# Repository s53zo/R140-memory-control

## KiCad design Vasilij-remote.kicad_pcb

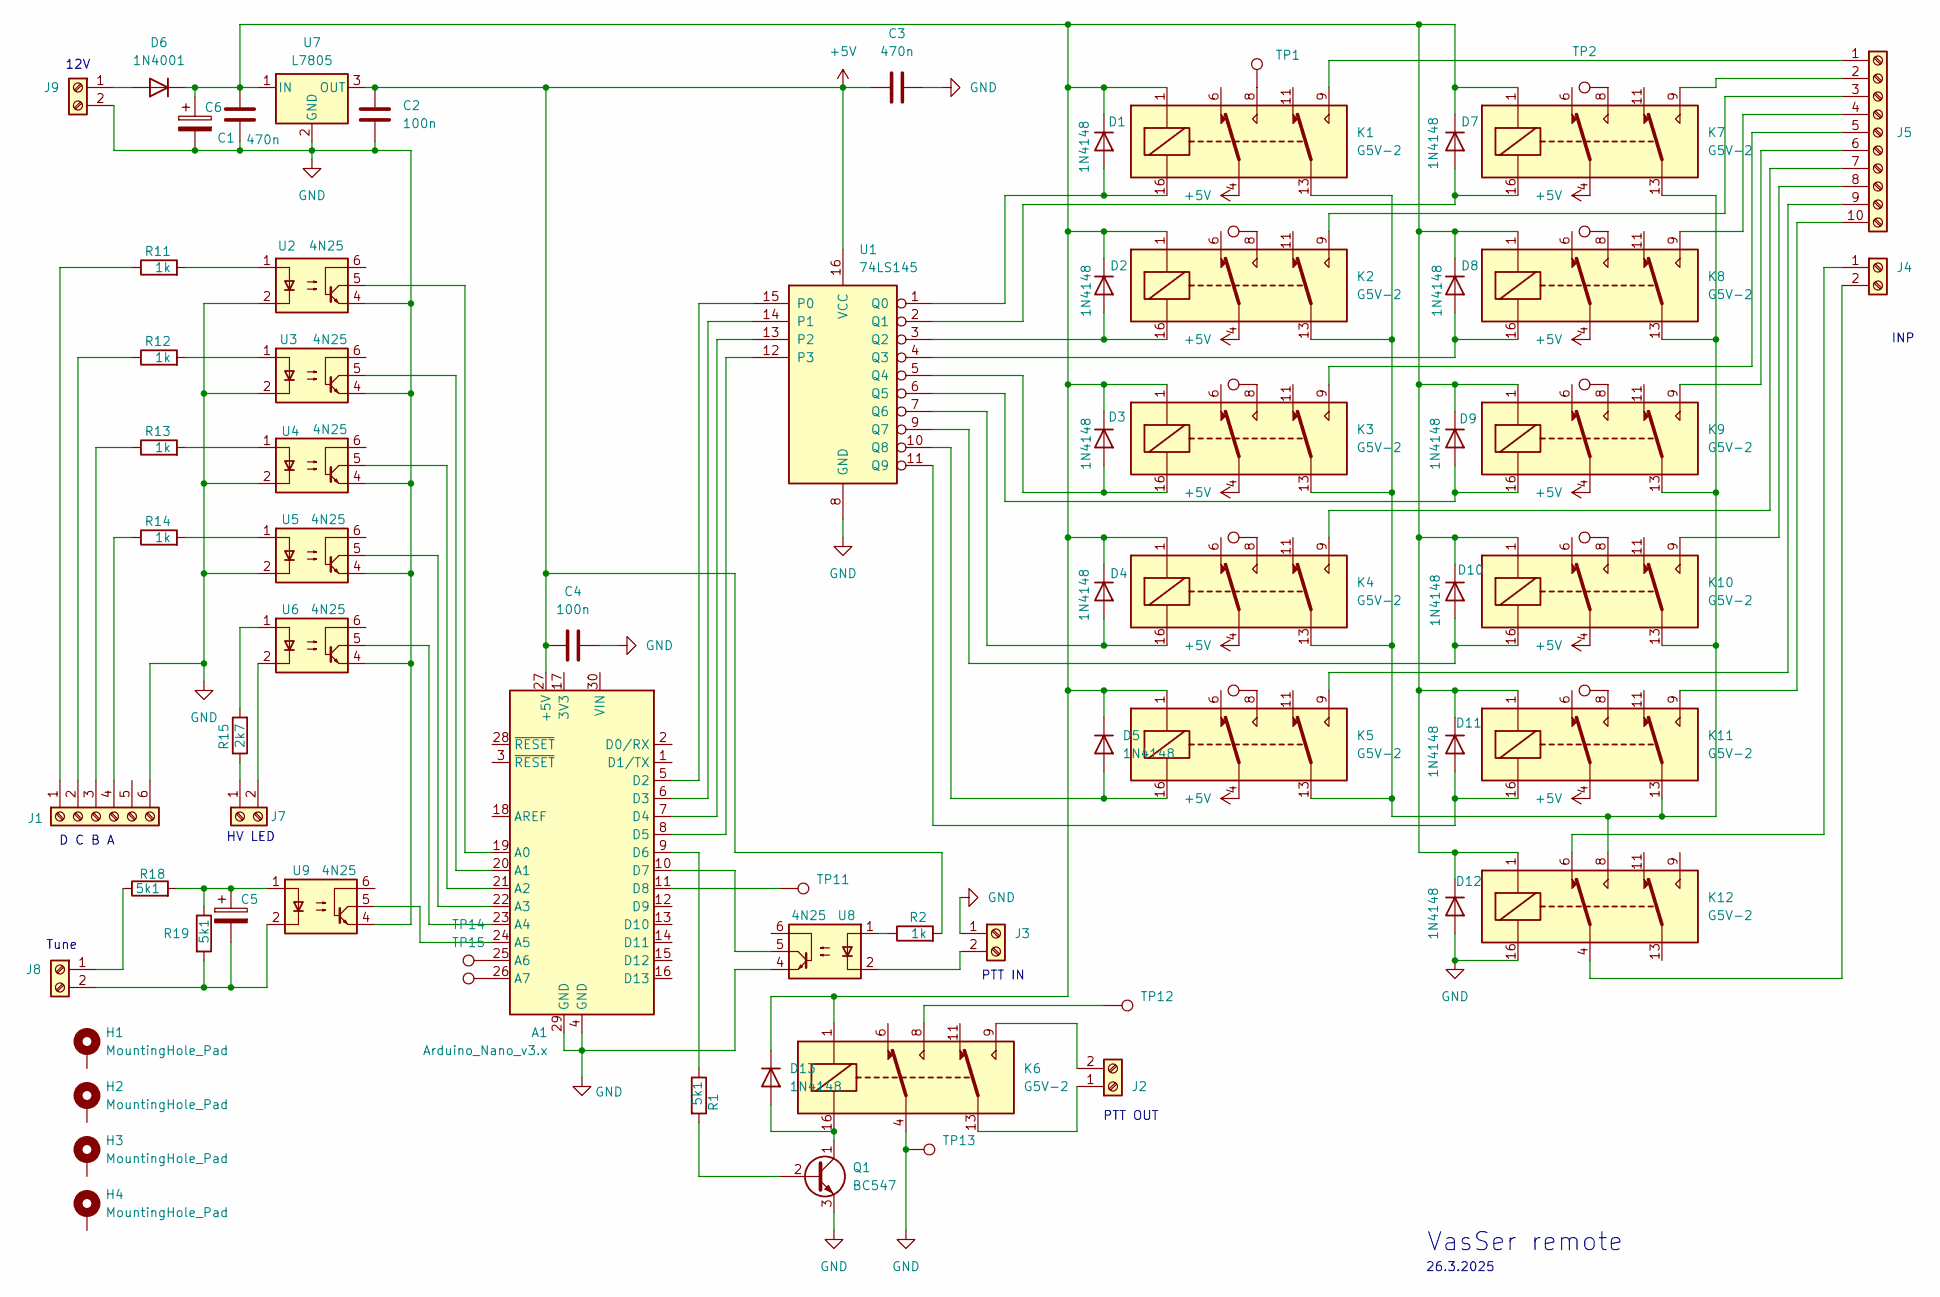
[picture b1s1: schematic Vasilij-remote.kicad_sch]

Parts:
A1: Arduino_Nano_v3.x; Arduino_Nano
C1, C3: 470n; C_Axial_L3.8mm_D2.6mm_P7.50mm_Horizontal
C2: 100n; C_Axial_L3.8mm_D2.6mm_P7.50mm_Horizontal
C4: 100n; C_Disc_D4.3mm_W1.9mm_P5.00mm
C5, C6: 100uF; CP_Radial_D5.0mm_P2.00mm
D1, D2, D3, D4, D5, D7, D8, D9, D10, D11, D12, D13: 1N4148; D_DO-34_SOD68_P7.62mm_Horizontal
D6: 1N4001; D_DO-41_SOD81_P10.16mm_Horizontal
H1, H2, H3, H4: MountingHole_Pad; MountingHole_3.2mm_M3_DIN965_Pad
J1: Screw_Terminal_01x06; TerminalBlock_Xinya_XY308-2.54-6P_1x06_P2.54mm_Horizontal
J2, J3, J4, J7, J8, J9: Screw_Terminal_01x02; TerminalBlock_Xinya_XY308-2.54-2P_1x02_P2.54mm_Horizontal
J5: Screw_Terminal_01x10; TerminalBlock_Xinya_XY308-2.54-10P_1x10_P2.54mm_Horizontal
K1, K2, K3, K4, K5, K6, K7, K8, K9, K10, K11, K12: G5V-2; Relay_DPDT_Omron_G5V-2
Q1: BC547; TO-92_Inline
R1, R18, R19: 5k1; R_Axial_DIN0204_L3.6mm_D1.6mm_P5.08mm_Horizontal
R2, R11, R12, R13, R14: 1k; R_Axial_DIN0204_L3.6mm_D1.6mm_P5.08mm_Horizontal
R15: 2k7; R_Axial_DIN0204_L3.6mm_D1.6mm_P5.08mm_Horizontal
TP1, TP2, TP3, TP4, TP5, TP6, TP7, TP8, TP9, TP10, TP11, TP12, TP13, TP14, TP15: TestPoint; Pin_D0.7mm_L6.5mm_W1.8mm_FlatFork
U1: 74LS145; DIP-16_W7.62mm
U2, U3, U4, U5, U6, U8, U9: 4N25; DIP-6_W7.62mm
U7: L7805; TO-220F-3_Vertical

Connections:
+5V: A1.27 (+5V), C2.1, C3.1, C4.1, K1.4, K2.4, K3.4, K4.4, K5.4, K7.4, K8.4, K9.4, K10.4, K11.4, R2.2, U1.16 (VCC), U7.3 (OUT)
GND: A1.4 (GND), A1.29 (GND), C1.2, C2.2, C3.2, C4.2, C6.2, D12.2 (A), J1.6, J3.1, J9.2, K6.4, K12.16, Q1.3 (E), TP13.1, U1.8 (GND), U2.2, U2.4, U3.2, U3.4, U4.2, U4.4, U5.2, U5.4, U6.4, U7.2 (GND), U8.4, U9.4
unnamed: A1.19 (A0), U2.5
unnamed: A1.20 (A1), U3.5
unnamed: A1.21 (A2), U4.5
unnamed: A1.22 (A3), U5.5
unnamed: A1.23 (A4), U6.5
unnamed: A1.24 (A5), U9.5
unnamed: A1.25 (A6), TP14.1
unnamed: A1.26 (A7), TP15.1
unnamed: A1.5 (D2), U1.15 (P0)
unnamed: A1.6 (D3), U1.14 (P1)
unnamed: A1.7 (D4), U1.13 (P2)
unnamed: A1.8 (D5), U1.12 (P3)
unnamed: A1.9 (D6), R1.1
unnamed: A1.10 (D7), U8.5
unnamed: A1.11 (D8), TP11.1
unnamed: C5.1, R18.2, R19.1, U9.1
unnamed: D1.2 (A), K1.16, U1.1 (Q0)
unnamed: C1.1, C6.1, D1.1 (K), D2.1 (K), D3.1 (K), D4.1 (K), D5.1 (K), D6.1 (K), D7.1 (K), D8.1 (K), D9.1 (K), D10.1 (K), D11.1 (K), D12.1 (K), D13.1 (K), K1.1, K2.1, K3.1, K4.1, K5.1, K6.1, K7.1, K8.1, K9.1, K10.1, K11.1, K12.1, U7.1 (IN)
unnamed: D2.2 (A), K2.16, U1.3 (Q2)
unnamed: D3.2 (A), K3.16, U1.5 (Q4)
unnamed: D4.2 (A), K4.16, U1.7 (Q6)
unnamed: D5.2 (A), K5.16, U1.10 (Q8)
unnamed: D6.2 (A), J9.1
unnamed: D7.2 (A), K7.16, U1.2 (Q1)
unnamed: D8.2 (A), K8.16, U1.4 (Q3)
unnamed: D9.2 (A), K9.16, U1.6 (Q5)
unnamed: D10.2 (A), K10.16, U1.9 (Q7)
unnamed: D11.2 (A), K11.16, U1.11 (Q9)
unnamed: D13.2 (A), K6.16, Q1.1 (C)
unnamed: J1.1, R11.1
unnamed: J1.2, R12.1
unnamed: J1.3, R13.1
unnamed: J1.4, R14.1
unnamed: J2.1, K6.13
unnamed: J2.2, K6.9
unnamed: J3.2, U8.2
unnamed: J4.1, K12.6
unnamed: J4.2, K12.4
unnamed: J5.1, K1.9
unnamed: J5.2, K7.9
unnamed: J5.3, K2.9
unnamed: J5.4, K8.9
unnamed: J5.5, K3.9
unnamed: J5.6, K9.9
unnamed: J5.7, K4.9
unnamed: J5.8, K10.9
unnamed: J5.9, K5.9
unnamed: J5.10, K11.9
unnamed: J7.1, R15.1
unnamed: J7.2, U6.2
unnamed: J8.1, R18.1
unnamed: C5.2, J8.2, R19.2, U9.2
unnamed: K1.8, TP1.1
unnamed: K1.13, K2.13, K3.13, K4.13, K5.13, K7.13, K8.13, K9.13, K10.13, K11.13, K12.8
unnamed: K2.8, TP4.1
unnamed: K3.8, TP5.1
unnamed: K4.8, TP7.1
unnamed: K5.8, TP8.1
unnamed: K6.8, TP12.1
unnamed: K7.8, TP2.1
unnamed: K8.8, TP3.1
unnamed: K9.8, TP6.1
unnamed: K10.8, TP9.1
unnamed: K11.8, TP10.1
unnamed: Q1.2 (B), R1.2
unnamed: R2.1, U8.1
unnamed: R11.2, U2.1
unnamed: R12.2, U3.1
unnamed: R13.2, U4.1
unnamed: R14.2, U5.1
unnamed: R15.2, U6.1

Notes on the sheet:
INP
26.3.2025
D C B A
HV LED
PTT IN
VasSer remote
PTT OUT
Tune
12V

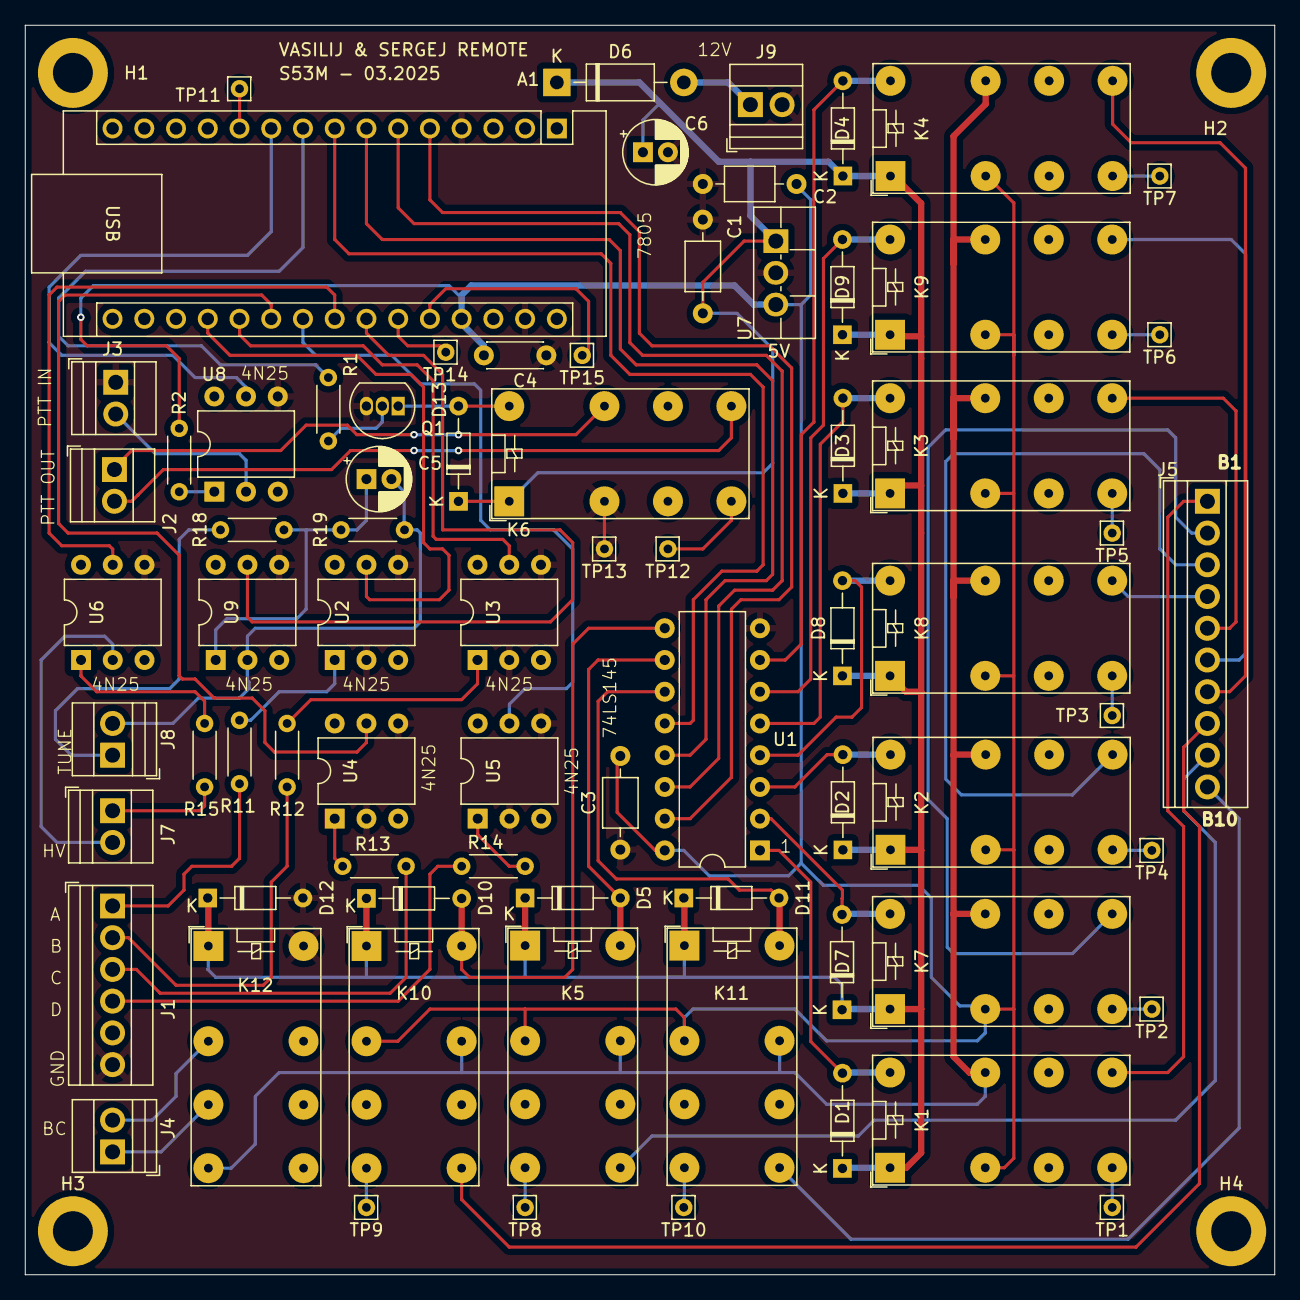
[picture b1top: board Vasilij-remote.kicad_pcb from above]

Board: 2 copper layers, 100.0 x 100.0 mm, 78 parts (0 on the bottom side), 73 nets.

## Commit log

2025-11-13 Add Vasilij remote design files
2025-11-13 Rename sergej.ino to sergej_basic.ino
2025-11-13 old version
    old version
2025-11-13 Adjust control pins and debug window
2025-11-16 Refactor PTT handling and background tasks
